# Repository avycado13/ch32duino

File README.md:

# CH32Duino
A Devboard made from an ultra cheap ch32v203

## Features
- Arduino micro-ish pinout
- USB-C Port
- Ultra-cheap (parts < 10$)

## Why?
I finished making a full scale arduino-esque board and I wanted to make another devboard. I chose to make one as cheap as I Could. I probably could have skimped even more on the usb socket and LDO, but I went with ones I knew about.

## BOM

| Qty | Reference | Value | Package | Description | Price | Link |
|---:|---|---|---|---|---:|---|
| 1 | U1 | CH32V203C8T6 | LQFP-48 (7 × 7 mm) | Main MCU | $0.8821 | [JLCPCB](https://jlcpcb.com/partdetail/WCH_Jiangsu_Qin_Heng-CH32V203C8T6/C3001172) |
| 1 | U2 | AMS1117-3.3 | SOT-223 | LDO, +5V to +3.3V | $0.2048 | [JLCPCB](https://jlcpcb.com/partdetail/Advanced_MonolithicSystems-AMS1117_33/C6186) |
| 1 | U3 | USB-C Receptacle | SMD | USB-C Port | $0.1869 | [JLCPCB](https://jlcpcb.com/partdetail/Korean_HropartsElec-TYPE_C_31_M12/C165948) |
| 2 | R1, R2 | 10K | 0805 | 10K 0805 Resistors | $0.0034 | [JLCPCB](https://jlcpcb.com/partdetail/18102-0805W8F1002T5E/C17414) |
| 2 | R3, R4 | 5.1K | 0805 | 5.1K 0805 Resistors | $0.0055 | [JLCPCB](https://jlcpcb.com/partdetail/28584-0805W8F5101T5E/C27834) |
| 2 | C1, C2 | 100nF | 0805 | 100nF 0805 Capacitors | $0.0205 | [JLCPCB](https://jlcpcb.com/partdetail/YAGEO-CC0805KRX7R9BB104/C49678) |
| 1 |  | | | PARTS SUBTOTAL (with minimum quantities): | $6.7640 |

## Firmware
For firmware, I am using ch32fun at the moment.

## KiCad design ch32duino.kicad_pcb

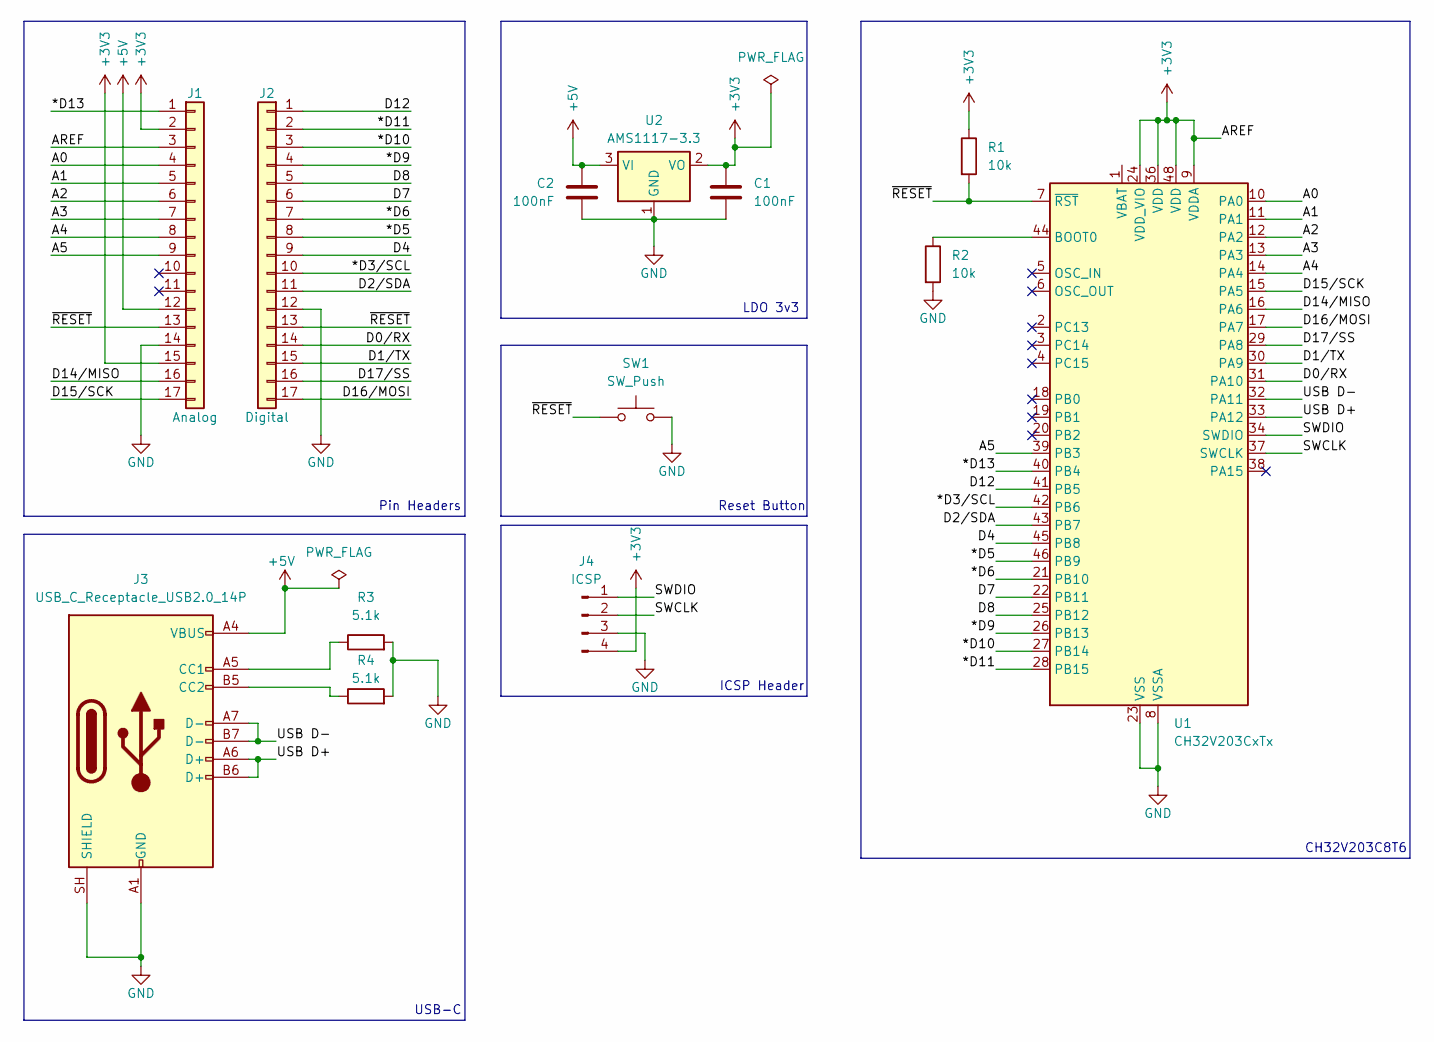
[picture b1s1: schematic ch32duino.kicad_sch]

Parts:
C1, C2: 100nF; C_0805_2012Metric_Pad1.18x1.45mm_HandSolder
J1: Analog; PinHeader_1x17_P2.54mm_Vertical
J2: Digital; PinHeader_1x17_P2.54mm_Vertical
J3: USB_C_Receptacle_USB2.0_14P; USB_C_Receptacle_HRO_TYPE-C-31-M-12; MPN TYPE-C-31-M-12; LCSC Part # C165948
J4: ICSP; PinHeader_1x04_P2.54mm_Vertical
R1, R2: 10k; R_0805_2012Metric_Pad1.20x1.40mm_HandSolder
R3, R4: 5.1k; R_0805_2012Metric_Pad1.20x1.40mm_HandSolder
SW1: SW_Push; SW_PUSH_6mm; MPN SH-6X6X5H-CJ; LCSC Part # C42416245
U1: CH32V203CxTx; LQFP-48_7x7mm_P0.5mm; MPN CH32V203C8T6; LCSC Part # C3001172
U2: AMS1117-3.3; SOT-223-3_TabPin2; MPN AMS1117-3.3; LCSC Part # C6186

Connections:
+3V3: C1.1, J1.2, J1.3, J1.15, J4.4, R1.1, U1.9 (VDDA), U1.24 (VDD_VIO), U1.36 (VDD), U1.48 (VDD), U2.2 (VO)
+5V: C2.1, J1.12, J3.A4 (VBUS), J3.A9 (VBUS), J3.B4 (VBUS), J3.B9 (VBUS), U2.3 (VI)
/*D3/SCL: J2.10, U1.42 (PB6)
/*D5: J2.8, U1.46 (PB9)
/*D6: J2.7, U1.21 (PB10)
/*D9: J2.4, U1.26 (PB13)
/*D10: J2.3, U1.27 (PB14)
/*D11: J2.2, U1.28 (PB15)
/*D13: J1.1, U1.40 (PB4)
/A0: J1.4, U1.10 (PA0)
/A1: J1.5, U1.11 (PA1)
/A2: J1.6, U1.12 (PA2)
/A3: J1.7, U1.13 (PA3)
/A4: J1.8, U1.14 (PA4)
/A5: J1.9, U1.39 (PB3)
/D0/RX: J2.14, U1.31 (PA10)
/D1/TX: J2.15, U1.30 (PA9)
/D2/SDA: J2.11, U1.43 (PB7)
/D4: J2.9, U1.45 (PB8)
/D7: J2.6, U1.22 (PB11)
/D8: J2.5, U1.25 (PB12)
/D12: J2.1, U1.41 (PB5)
/D14/MISO: J1.16, U1.16 (PA6)
/D15/SCK: J1.17, U1.15 (PA5)
/D16/MOSI: J2.17, U1.17 (PA7)
/D17/SS: J2.16, U1.29 (PA8)
/SWCLK: J4.2, U1.37 (SWCLK)
/SWDIO: J4.1, U1.34 (SWDIO)
/USB D+: J3.A6 (D+), J3.B6 (D+), U1.33 (PA12)
/USB D-: J3.A7 (D-), J3.B7 (D-), U1.32 (PA11)
/~RESET: J1.13, J2.13, R1.2, SW1.1, U1.7 (~RST)
GND: C1.2, C2.2, J1.14, J2.12, J3.A1 (GND), J3.A12 (GND), J3.B1 (GND), J3.B12 (GND), J3.SH (SHIELD), J4.3, R2.2, R3.2, R4.2, SW1.2, U1.8 (VSSA), U1.23 (VSS), U1.35 (VSS), U1.47 (VSS), U2.1 (GND)
unnamed: J3.A5 (CC1), R3.1
unnamed: J3.B5 (CC2), R4.1
unnamed: R2.1, U1.44 (BOOT0)

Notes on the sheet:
ICSP Header
Reset Button
USB-C
LDO 3v3
Pin Headers
CH32V203C8T6

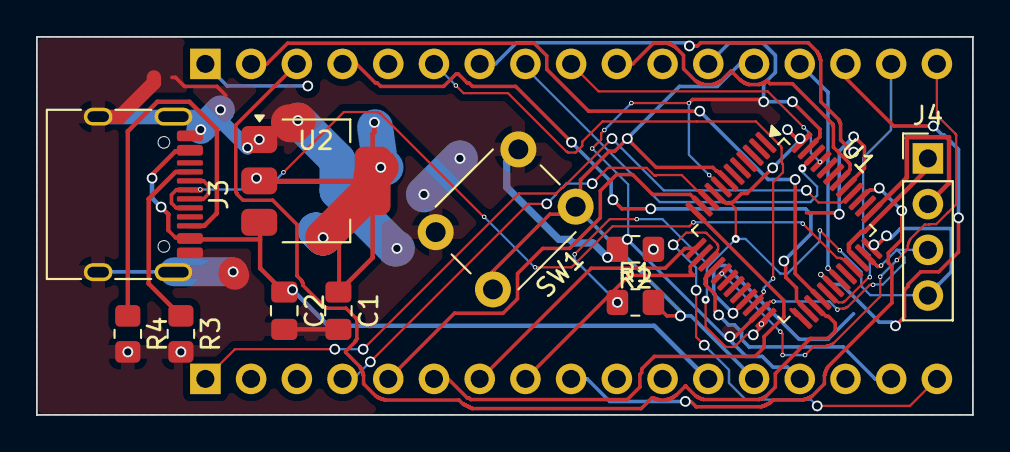
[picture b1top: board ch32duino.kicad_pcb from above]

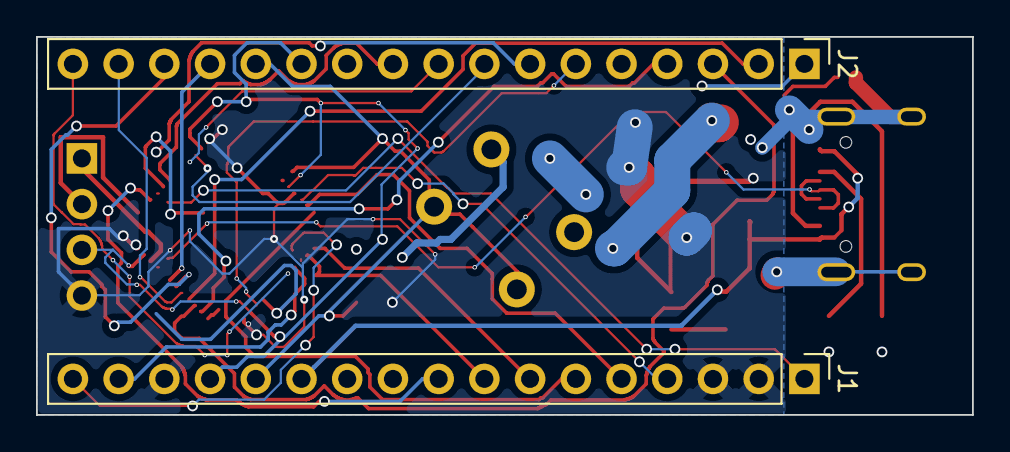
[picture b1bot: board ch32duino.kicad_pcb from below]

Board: 2 copper layers, 52.0 x 21.0 mm, 13 parts (2 on the bottom side), 35 nets.

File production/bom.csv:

Designator,Footprint,Quantity,Value,LCSC Part #
"C1, C2",0805,2,100nF,
J1,PinHeader_1x17_P2.54mm_Vertical,1,Analog,
J2,PinHeader_1x17_P2.54mm_Vertical,1,Digital,
J3,USB_C_Receptacle_HRO_TYPE-C-31-M-12,1,USB_C_Receptacle_USB2.0_14P,C165948
J4,PinHeader_1x04_P2.54mm_Vertical,1,ICSP,
"R1, R2",0805,2,10k,
"R3, R4",0805,2,5.1k,
SW1,SW_PUSH_6mm,1,SW_Push,C42416245
U1,LQFP-48_7x7mm_P0.5mm,1,CH32V203CxTx,C3001172
U2,SOT-223-3_TabPin2,1,AMS1117-3.3,C6186
